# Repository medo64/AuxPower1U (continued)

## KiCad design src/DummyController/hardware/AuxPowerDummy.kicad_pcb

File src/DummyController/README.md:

# AuxPower1U: DummyController

Features:
* 5 DC inputs (input 1 has to be 9-15V)
* 5 DC outputs
* always connected output; no logic

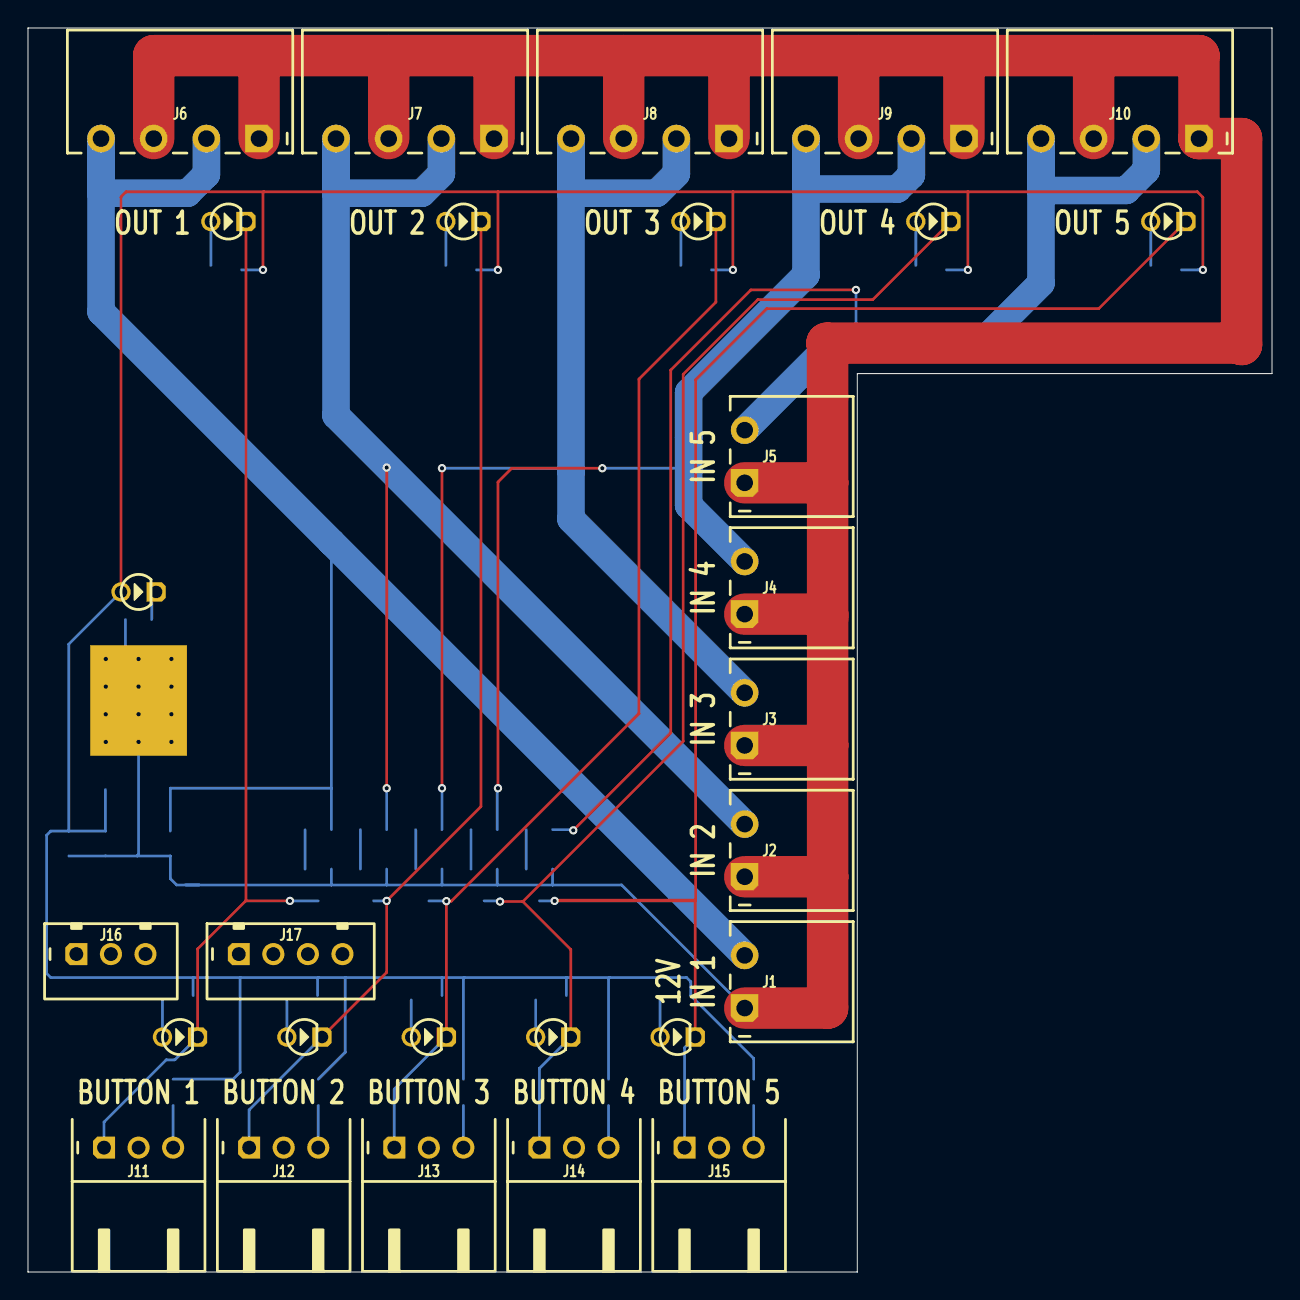
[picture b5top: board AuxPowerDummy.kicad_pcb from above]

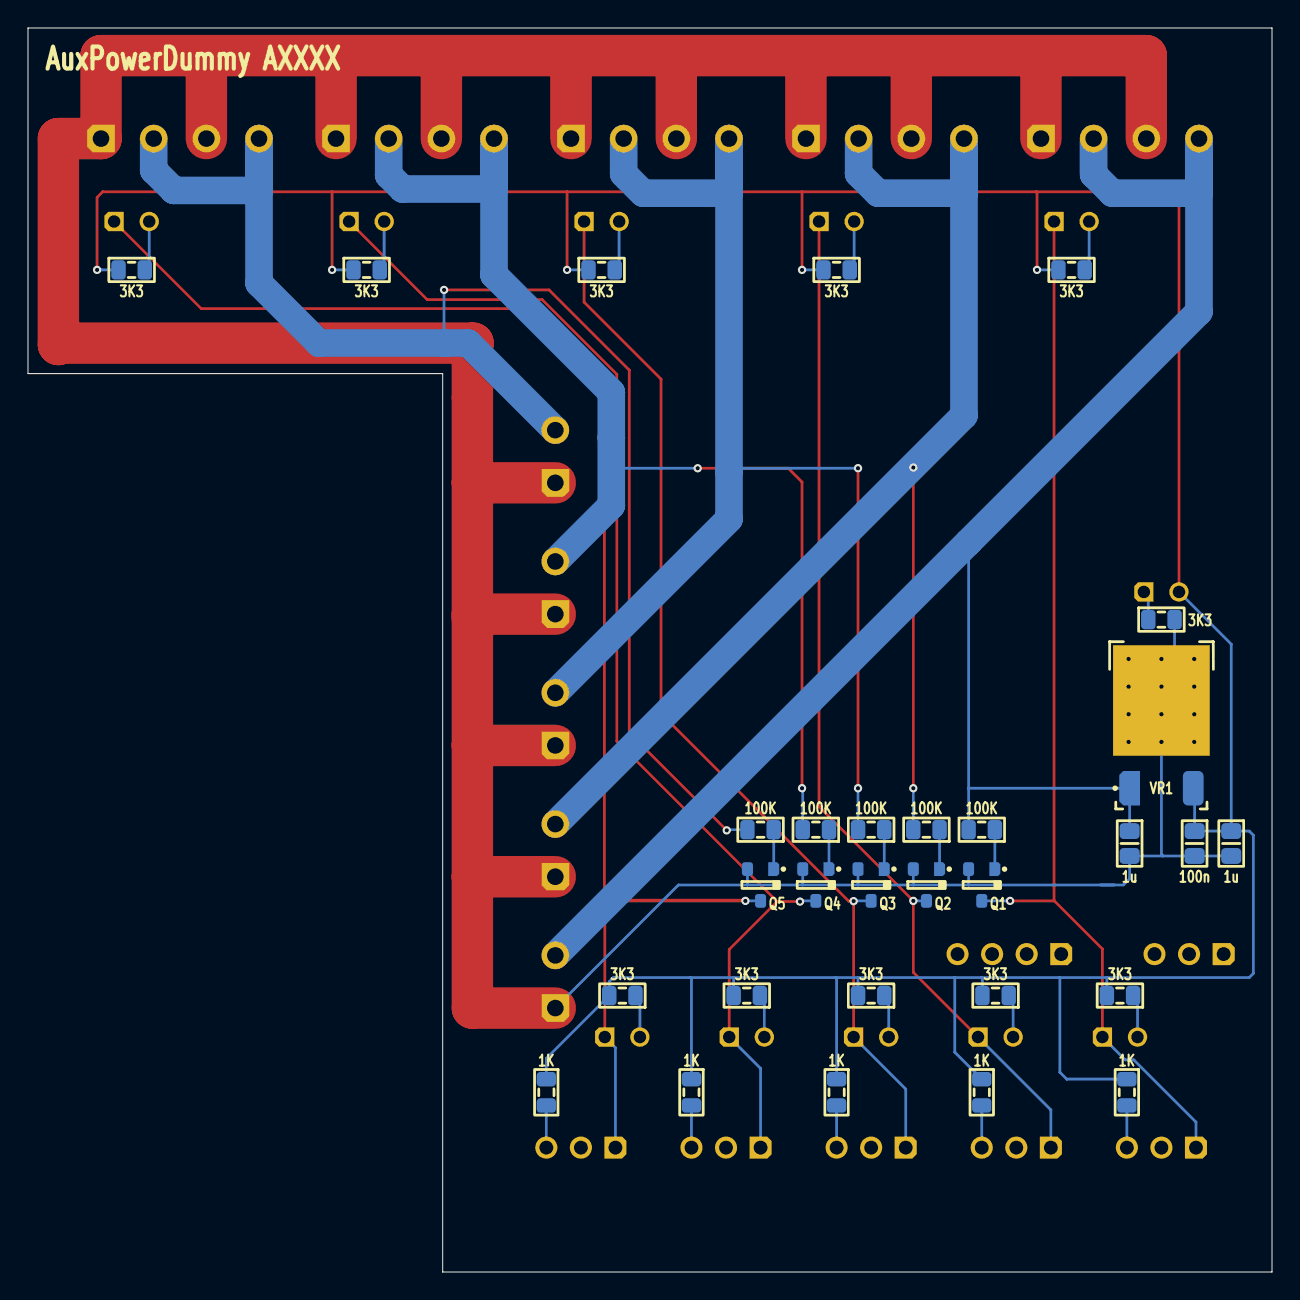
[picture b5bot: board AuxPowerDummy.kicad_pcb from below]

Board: 2 copper layers, 90.0 x 90.0 mm, 58 parts (30 on the bottom side), 33 nets.

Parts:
C1: 100n; C (0805)
C2, C3: 1u; C (0805)
DS1, DS2, DS3, DS4, DS5, DS6, DS7, DS8, DS9, DS10, DS11: LED; DS (D3.0)
J1, J2, J3, J4, J5: MC 1,5/2; J Phoenix MC (2w)
J6, J7, J8, J9, J10: MC 1,5/4; J Phoenix MC (4w)
J11, J12, J13, J14, J15: S3B-XH-A; J JST XH S (3w)
J16: B3B-XH-A; J JST XH B [UART] (3w)
J17: B4B-XH-A; J JST XH B [I2C] (4w)
Q1, Q2, Q3, Q4, Q5: BC846B,235; Q Transistor NPN (SOT23-3)
R1, R2, R3, R4, R5: 1K; R (0805)
R6, R7, R8, R9, R10, R11, R12, R13, R14, R15, R16: 3K3; R (0805)
R17, R18, R19, R20, R21: 100K; R (0805)
VR1: AS7805ADTR; VR Linear 5V 1000mA [AS7805ADTR-G1] (TO252-2')

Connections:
5V: C1.2, C3.2, DS11.2, R1.2, R2.2, R3.2, R4.2, R5.2, R6.2, R7.2, R8.2, R9.2, R10.2, R11.1, R12.1, R13.1, R14.1, R15.1, VR1.3
BASE_SW1: Q1.1, R17.2
BASE_SW2: Q2.1, R18.2
BASE_SW3: Q3.1, R19.2
BASE_SW4: Q4.1, R20.2
BASE_SW5: Q5.1, R21.2
BUTTON1_LED: J11.3, R1.1
BUTTON2_LED: J12.3, R2.1
BUTTON3_LED: J13.3, R3.1
BUTTON4_LED: J14.3, R4.1
BUTTON5_LED: J15.3, R5.1
GND: C1.1, C2.1, C3.1, J1.1, J2.1, J3.1, J4.1, J5.1, J6.1, J6.3, J7.1, J7.3, J8.1, J8.3, J9.1, J9.3, J10.1, J10.3, Q1.2, Q2.2, Q3.2, Q4.2, Q5.2, R16.1, VR1.2
GND_SW1: DS1.1, DS6.1, J11.1, Q1.3
GND_SW2: DS2.1, DS7.1, J12.1, Q2.3
GND_SW3: DS3.1, DS8.1, J13.1, Q3.3
GND_SW4: DS4.1, DS9.1, J14.1, Q4.3
GND_SW5: DS5.1, DS10.1, J15.1, Q5.3
INPUT1: C2.2, J1.2, J6.2, J6.4, R17.1, VR1.1
INPUT2: J2.2, J7.2, J7.4, R18.1
INPUT3: J3.2, J8.2, J8.4, R19.1
INPUT4: J4.2, J9.2, J9.4, R20.1
INPUT5: J5.2, J10.2, J10.4, R21.1
LED_BUTTON_INT_1: DS1.2, R11.2
LED_BUTTON_INT_2: DS2.2, R12.2
LED_BUTTON_INT_3: DS3.2, R13.2
LED_BUTTON_INT_4: DS4.2, R14.2
LED_BUTTON_INT_5: DS5.2, R15.2
LED_OUT1: DS6.2, R6.1
LED_OUT2: DS7.2, R7.1
LED_OUT3: DS8.2, R8.1
LED_OUT4: DS9.2, R9.1
LED_OUT5: DS10.2, R10.1
LED_POWER: DS11.1, R16.2

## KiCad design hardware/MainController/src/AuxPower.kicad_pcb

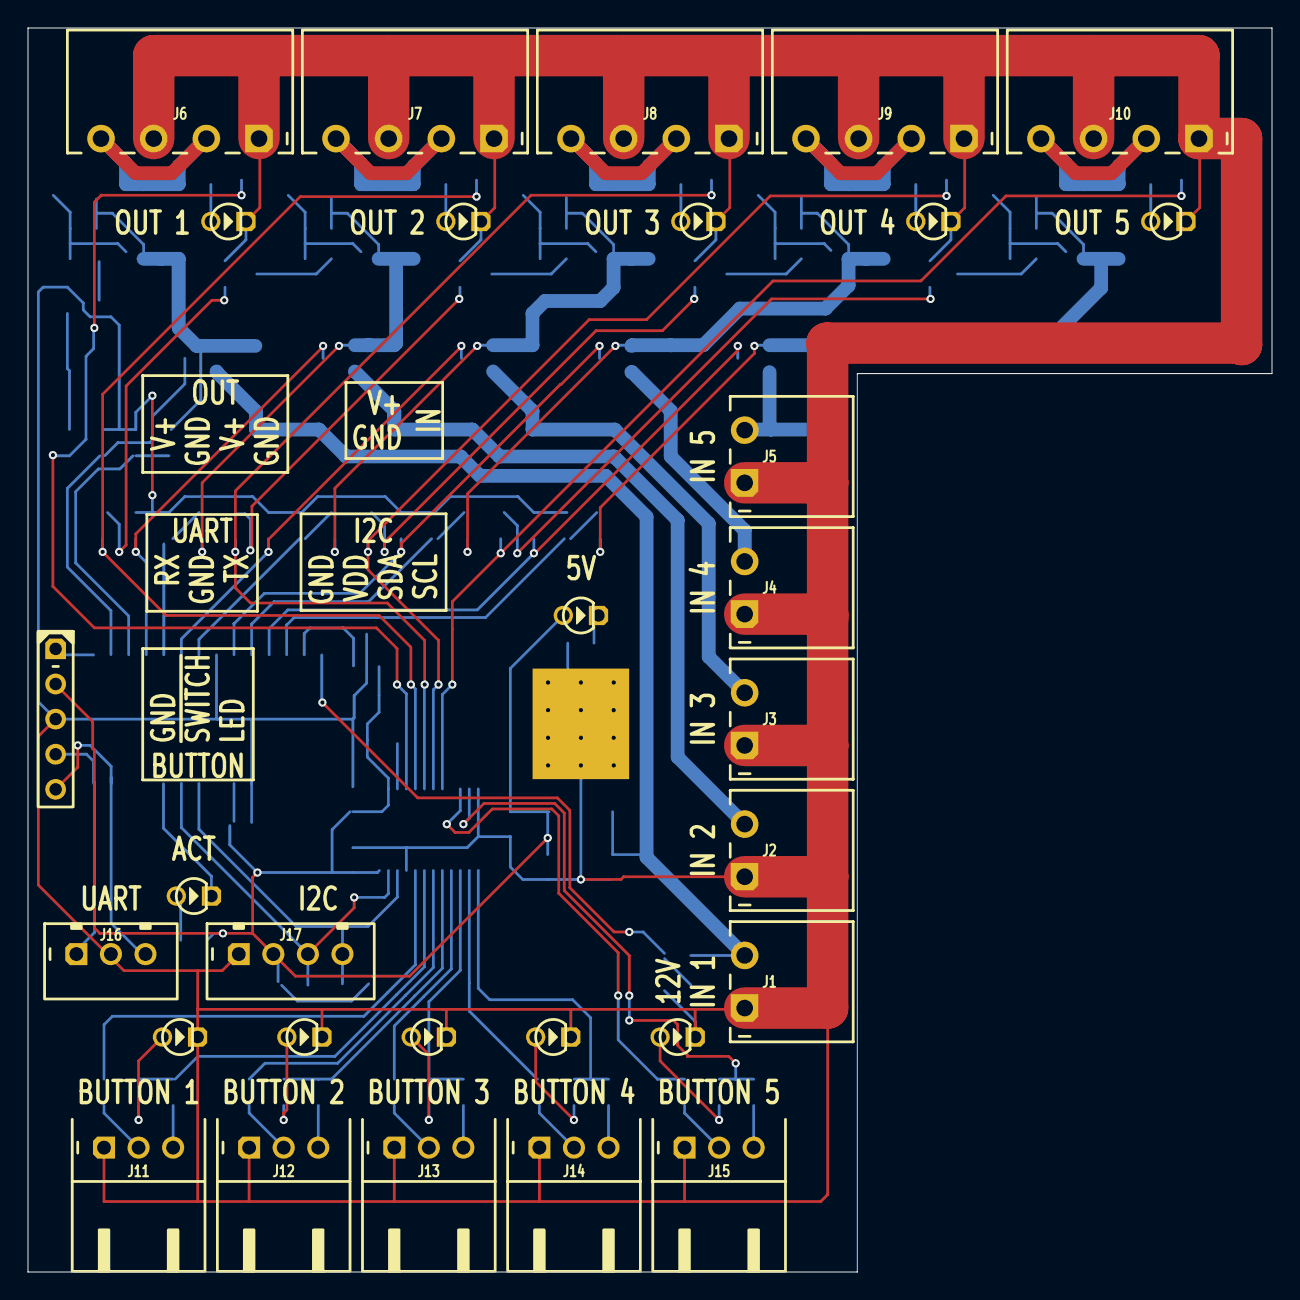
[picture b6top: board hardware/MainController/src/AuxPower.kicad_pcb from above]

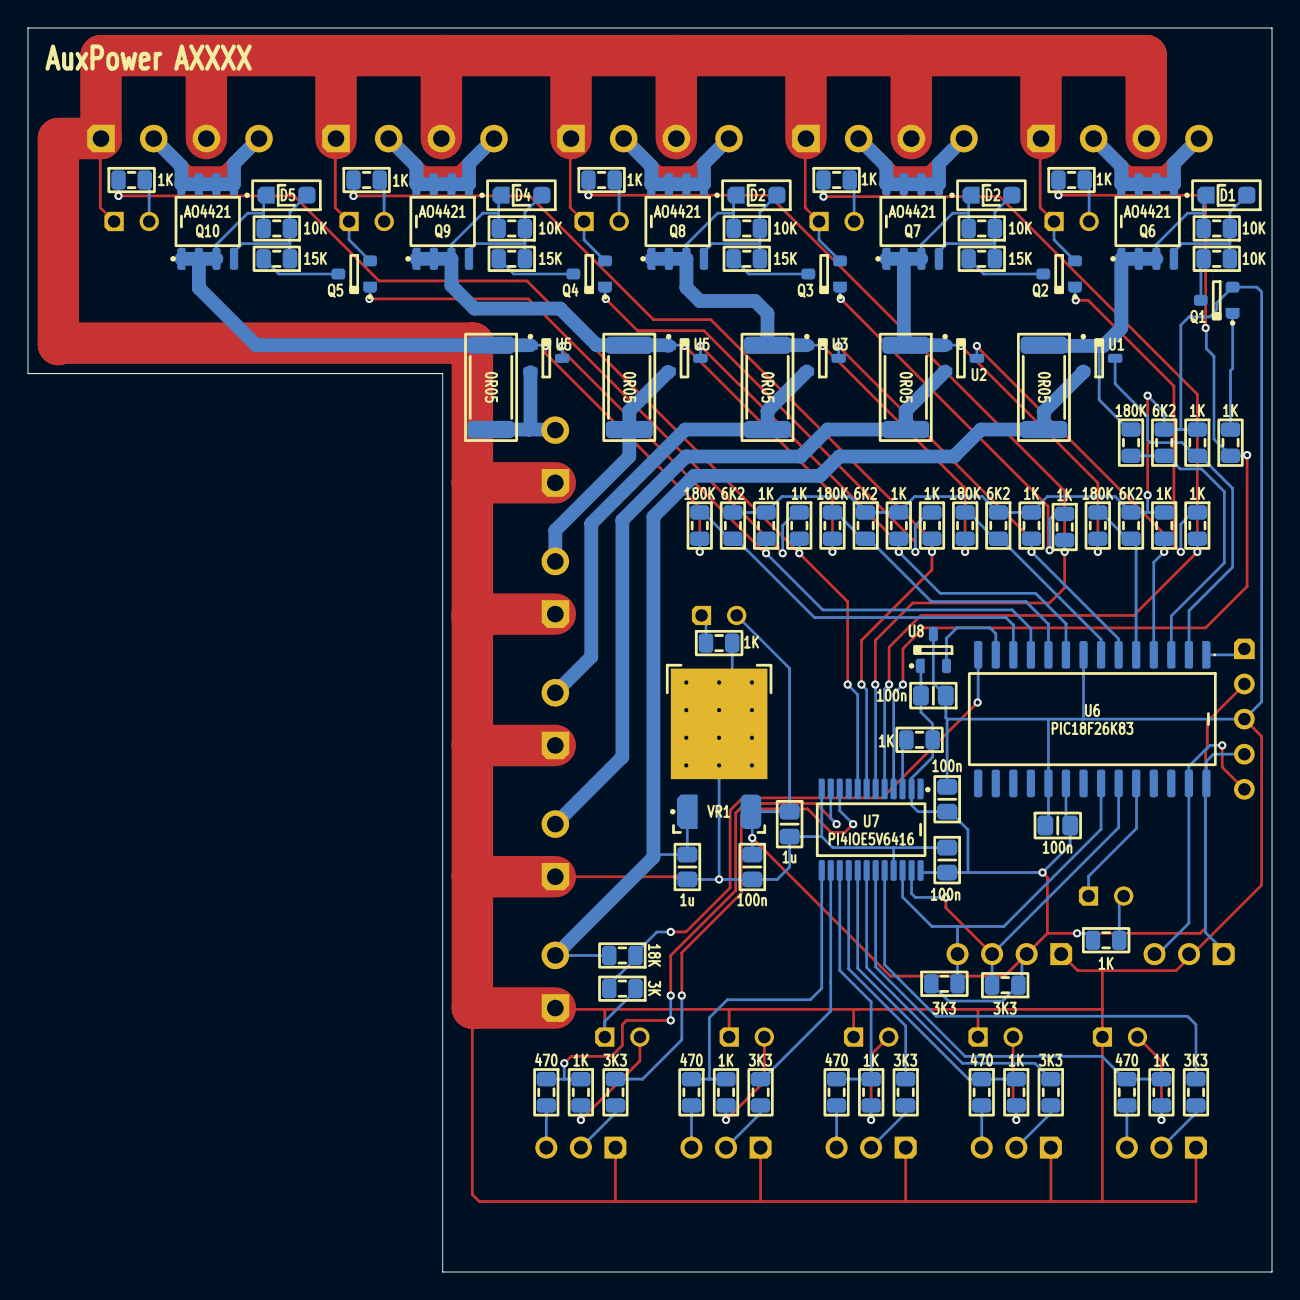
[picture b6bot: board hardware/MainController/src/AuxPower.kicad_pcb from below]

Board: 2 copper layers, 90.0 x 90.0 mm, 123 parts (93 on the bottom side), 88 nets.

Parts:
C1, C2, C3, C4, C5: 100n; C (0805)
C6, C7: 1u; C (0805)
D1, D2, D2#2, D4, D5: BZT52C12; D Zener (SOD123FL)
DS1, DS2, DS3, DS4, DS5, DS6, DS7, DS8, DS9, DS10, DS11, DS12: LED; DS (D3.0)
ICSP: Microchip PIC; ICSP PIC Pogo (5w)
J1, J2, J3, J4, J5: MC 1,5/2; J Phoenix MC (2w)
J6, J7, J8, J9, J10: MC 1,5/4; J Phoenix MC (4w)
J11, J12, J13, J14, J15: S3B-XH-A; J JST XH S (3w)
J16: B3B-XH-A; J JST XH B [UART] (3w)
J17: B4B-XH-A; J JST XH B [I2C] (4w)
Q1, Q2, Q3, Q4, Q5: BC846B,235; Q Transistor NPN (SOT23-3)
Q6, Q7, Q8, Q9, Q10: AO4421; Q MOSFET-P (SO-8)
R1, R2, R3, R4, R5: 0R05; R (2512)
R6, R7, R8, R9, R10: 470; R (0805)
R11, R12, R13, R14, R15, R16, R17, R18, R19, R20, R21, R22, R23, R24, R25, R26, R27, R28, R29, R30, R31, R32, R33: 1K; R (0805)
R34: 3K; R (0805)
R35, R36, R37, R38, R39, R40, R41: 3K3; R (0805)
R42, R43, R44, R45, R46: 6K2; R (0805)
R47, R48, R49, R50, R51, R52: 10K; R (0805)
R53, R54, R55, R56: 15K; R (0805)
R57: 18K; R (0805)
R58, R59, R60, R61, R62: 180K; R (0805)
U1, U2, U3, U5, U5#2: ZXCT1009; U Current Monitor [ZXCT1009] (SOT23-3)
U6: PIC18F26K83; U Micro [PIC18F26K83] (SOIC-28)
U7: PI4IOE5V6416; U Expander I2C [PI4IOE5V6416LEX] (TSSOP-24)
U8: MCP9701; U Temperature Analog [MCP9701] (SOT23-3)
VR1: AS7805ADTR; VR Linear 5V 1000mA [AS7805ADTR-G1] (TO252-2')

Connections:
5V: C1.2, C2.1, C3.1, C4.1, C5.1, C6.2, DS11.2, ICSP.2, J17.2, R32.2, R33.2, R40.2, R41.2, U6.20, U7.2, U7.24, U8.1, VR1.3
ADC_CURRENT1: R16.1, U1.3, U6.2
ADC_CURRENT2: R17.1, U2.3, U6.4
ADC_CURRENT3: R18.1, U3.3, U6.6
ADC_CURRENT4: R19.1, U5.3, U6.9
ADC_CURRENT5: R20.1, U5#2.3, U6.11
ADC_TEMPERATURE: U6.13, U8.2
ADC_VOLTAGE1: R42.1, R58.1, U6.3
ADC_VOLTAGE2: R43.1, R59.2, U6.5
ADC_VOLTAGE3: R44.1, R60.2, U6.7
ADC_VOLTAGE4: R45.1, R61.2, U6.10
ADC_VOLTAGE5: R46.1, R62.2, U6.12
ADC_VOLTAGE_IN: R34.1, R57.2, U6.14
BASE1: Q1.1, R11.1
BASE2: Q2.1, R12.2
BASE3: Q3.1, R13.2
BASE4: Q4.1, R14.2
BASE5: Q5.1, R15.2
BUTTON1_LED: J11.3, R6.1
BUTTON1_SWITCH: J11.2, R35.1
BUTTON2_LED: J12.3, R7.1
BUTTON2_SWITCH: J12.2, R36.1
BUTTON3_LED: J13.3, R8.1
BUTTON3_SWITCH: J13.2, R37.1
BUTTON4_LED: J14.3, R9.1
BUTTON4_SWITCH: J14.2, R38.1
BUTTON5_LED: J15.3, R10.1
BUTTON5_SWITCH: J15.2, R39.1
COLLECTOR1: Q1.3, R48.1
COLLECTOR2: Q2.3, R53.1
COLLECTOR3: Q3.3, R54.1
COLLECTOR4: Q4.3, R55.1
COLLECTOR5: Q5.3, R56.1
EXPANDER_RESET: R33.1, U7.3
GATE1: D1.2, Q6.4, R47.2, R48.2
GATE2: D2#2.2, Q7.4, R49.2, R53.2
GATE3: D2.2, Q8.4, R50.2, R54.2
GATE4: D4.2, Q9.4, R51.2, R55.2
GATE5: D5.2, Q10.4, R52.2, R56.2
GND: C1.1, C2.2, C3.2, C4.2, C5.2, C6.1, C7.1, DS1.1, DS2.1, DS3.1, DS4.1, DS5.1, DS6.1, DS7.1, DS8.1, DS9.1, DS10.1, ICSP.3, J1.1, J2.1, J3.1, J4.1, J5.1, J6.1, J6.3, J7.1, J7.3, J8.1, J8.3, J9.1, J9.3, J10.1, J10.3, J11.1, J12.1, J13.1, J14.1, J15.1, J16.2, J17.1, Q1.2, Q2.2, Q3.2, Q4.2, Q5.2, R16.2, R17.2, R18.2, R19.2, R20.2, R31.1, R34.2, R42.2, R43.2, R44.2, R45.2, R46.2, U6.8, U6.19, U7.12, U7.21, U8.3, VR1.2
I2C_SCL: J17.4, R41.1, U6.22, U7.22
I2C_SDA: J17.3, R40.1, U6.23, U7.23
ICSP_VPP: ICSP.1, U6.1
INPUT1: C7.2, J1.2, R1.1, R57.1, U1.2, VR1.1
INPUT1': D1.1, Q6.1, Q6.2, Q6.3, R1.2, R47.1, R58.2, U1.1
INPUT2: J2.2, R2.1, U2.2
INPUT2': D2#2.1, Q7.1, Q7.2, Q7.3, R2.2, R49.1, R59.1, U2.1
INPUT3: J3.2, R3.1, U3.2
INPUT3': D2.1, Q8.1, Q8.2, Q8.3, R3.2, R50.1, R60.1, U3.1
INPUT4: J4.2, R4.1, U5.2
INPUT4': D4.1, Q9.1, Q9.2, Q9.3, R4.2, R51.1, R61.1, U5.1
INPUT5: J5.2, R5.1, U5#2.2
INPUT5': D5.1, Q10.1, Q10.2, Q10.3, R5.2, R52.1, R62.1, U5#2.1
IN_BUTTON1_SWITCH: R35.2, U7.20
IN_BUTTON2_SWITCH: R36.2, U7.18
IN_BUTTON3_SWITCH: R37.2, U7.16
IN_BUTTON4_SWITCH: R38.2, U7.14
IN_BUTTON5_SWITCH: R39.2, U7.10
LED_ACTIVITY: DS12.2, R32.1
LED_BUTTON_INT_1: DS1.2, R26.1
LED_BUTTON_INT_2: DS2.2, R27.1
LED_BUTTON_INT_3: DS3.2, R28.1
LED_BUTTON_INT_4: DS4.2, R29.1
LED_BUTTON_INT_5: DS5.2, R30.1
LED_OUT_1: DS6.2, R21.1
LED_OUT_2: DS7.2, R22.1
LED_OUT_3: DS8.2, R23.1
LED_OUT_4: DS9.2, R24.1
LED_OUT_5: DS10.2, R25.1
LED_POWER: DS11.1, R31.2
OUTPUT1: J6.2, J6.4, Q6.5, Q6.6, Q6.7, Q6.8
OUTPUT2: J7.2, J7.4, Q7.5, Q7.6, Q7.7, Q7.8
OUTPUT3: J8.2, J8.4, Q8.5, Q8.6, Q8.7, Q8.8
OUTPUT4: J9.2, J9.4, Q9.5, Q9.6, Q9.7, Q9.8
OUTPUT5: J10.2, J10.4, Q10.5, Q10.6, Q10.7, Q10.8
OUT_ACTIVITY: DS12.1, U6.24
OUT_BUTTON1_LED: R6.2, R26.2, U7.19
OUT_BUTTON2_LED: R7.2, R27.2, U7.17
OUT_BUTTON3_LED: R8.2, R28.2, U7.15
OUT_BUTTON4_LED: R9.2, R29.2, U7.13
OUT_BUTTON5_LED: R10.2, R30.2, U7.11
OUT_OUTPUT1: R11.2, R21.2, U7.4
OUT_OUTPUT2: R12.1, R22.2, U7.5
OUT_OUTPUT3: R13.1, R23.2, U7.6
OUT_OUTPUT4: R14.1, R24.2, U7.7
OUT_OUTPUT5: R15.1, R25.2, U7.8
UART_RX ICSP_DAT: ICSP.4, J16.1, U6.28
UART_TX ICSP_CLK: ICSP.5, J16.3, U6.27

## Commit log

2024-08-17 Added DellTrigger sub-project
2024-08-17 Added aluminium plate model
2024-08-17 Added fan controller
2024-08-17 Fancontroller supports 4 fans
2024-08-18 Added requirements
2024-08-18 Added features
2024-08-18 Added DellTrigger schematics
2024-08-18 Added case selection
2024-08-18 Minor changes
2024-08-18 Added FanController schematics
2024-08-19 Changed DellTrigger diode to zener
2024-08-20 Added AC grommet
2024-08-20 Fixed hole diameter to 2.5mm
2024-08-21 Replaced MCP9700A with MCP9701A
2024-08-22 Added initial AuxPower
2024-08-23 Adjusted resistors a bit
2024-08-23 Added part list for controller
2024-08-23 Swapped PIC for SOIC variant
2024-08-23 Fixed fan connector count on FanController
2024-08-27 Moved silkscreen descriptions a bit
2024-08-27 Moving directory
2024-08-27 Updated models to have PTH holes on both sides
2024-08-27 Updated PTH components to have soldermask opening on both sides
2024-08-27 Moved GND line to look nicer
2024-08-29 Increasing resistors to account for 55V supply
2024-08-29 Added equipment setup
2024-08-29 Redesigned FanController board
2024-08-29 Renaming blog posts
2024-08-29 Added more explanation for DellTrigger
2024-08-29 Added UPS description
2024-08-30 Added AC grommet model
2024-08-30 Added OLED model
2024-09-01 Updated oled chasis tolerances
2024-09-01 Added alignment blocks
2024-09-02 Updated OLED model
2024-09-07 Additional OLED model update
2024-09-08 Added DellTrigger test
2024-09-09 Added shroud to alignment blocks
2024-09-11 Added case retainers
2024-09-11 Renamed drill template file
2024-09-12 Resizing PS retainers a bit
2024-09-12 Added chamfer to PS clips top
2024-09-12 A bit more messing with PS retainers
2024-09-13 More model updates
2024-09-14 Updated PS rails to be full length
2024-09-14 Added fan braces
2024-09-14 Add fan back brace (needs rework)
2024-09-14 Updated DC drill template
2024-09-14 Added alu plate fixup
2024-09-15 Refactoring fan brace
2024-09-15 Adjusted drill template for DC
2024-09-15 Added PCB case models
2024-09-15 Changed drill size for aluminium plate
2024-09-15 Adding parts
2024-09-15 Refactoring PCB retainer model
2024-09-15 Added extra parts
2024-09-16 Added stopped to OLED model
2024-09-16 Added fixup for audio 3.5mm jack
2024-09-17 Adjusted depth for main controller box
2024-09-17 Added PS story to docs
2024-09-17 Deeper cutouts for edge connectors
2024-09-17 Cutting edges some more
2024-09-17 More adjusting for PCB boxes
2024-09-18 Reorganizing directories
2024-09-18 Initial FanController project
2024-09-19 Adjusted PWM behavior
2024-09-19 FanController: temperature sensitive code
2024-09-19 Using moving average
2024-09-19 Updated 12F1501 model
2024-09-19 Added pin usage table for FanController
2024-09-19 Added pin usage for MainController
2024-09-22 Adjusted rail model to have pass-through for fan wires
2024-09-22 MainController: Fixing components
2024-09-22 MainController: Moved Activity LED a bit
2024-09-22 MainController: initial blink
2024-09-22 MainController: added ticker
2024-09-23 Initial working OLED communication
2024-09-23 Shortening code a bit
2024-09-23 Adding cooling blog post
2024-09-23 Refactoring file names
2024-09-23 Added IO expander outputs
2024-09-23 Added button input
2024-09-23 Refactoring i2c functions
2024-09-24 MainController: parametrising 18F module
2024-09-24 Readded I2c master code for PIC16F1454
2024-09-24 MainController: Added summary page
2024-09-25 MainController: Added ADC measurements
2024-09-26 Updated PIC
2024-09-26 Added test mode
2024-09-26 MainController: Adding forgotten 1K to GND for current monitor
2024-09-26 MainController: adjusting trace widths a bit
2024-09-26 MainController: enter test mode by holding button 1 and 5 together
2024-09-26 MainController: added usage
2024-09-27 Added wire colors
2024-09-27 Adding inverse writing for OLED
2024-09-27 Added progress bar
2024-09-27 Rounding all values up
2024-09-27 Added 8x averaging
2024-09-27 Bigger progress bar
2024-09-28 Added first fan controller post
2024-09-28 MainController: added open-drain outputs for rev B
2024-09-29 MainController: making output open-drain
2024-09-29 MainController: Changed transistor base resistor to 10K
2024-09-29 MainController: double-sampling ADC
2024-09-29 MainController: test mode shows display rate
2024-09-29 Added 5V reading to tests
2024-09-29 MainController: added die temperature reading to test mode
2024-09-29 MainController: Changed ZXCT1009 to HV7801
2024-09-29 Slighlty higher wattage resistor to cover for 8A range
2024-09-29 MainController: moved UART lines
2024-09-29 FanController: updated startup sequence
2024-09-29 MainController: Updated silkscreen
2024-09-30 Initial code for button handling
2024-09-30 Front LED state follows buttons
2024-09-30 MainController: added markers for channels that are on
2024-09-30 MainController: double-click to close summary
2024-10-02 Setting output together with LEDs
2024-10-02 Fixed OLED blinking
2024-10-02 MainController: fixing LEDs after reset from off state
2024-10-02 MainController: no need for setting LED and out manually
2024-10-03 MainController: prepping for settings load/save
2024-10-03 MainController: adjusting voltage dividers
2024-10-06 FanController: Both 1x4 and 2x2 variants available
2024-10-07 FanController: added post
2024-10-09 MainController: added settings save/load
2024-10-12 fixed typo
2024-10-12 Added basic UART and start of PPS
2024-10-12 Improved PPS
2024-10-12 Finished UART output
2024-10-12 MainController: added UART input
2024-10-13 MainController: added I UART command
2024-10-13 MainController: adjusting communication a bit
2024-10-13 MainController: fixed display bug
2024-10-13 MainController: Refactoring Uart
2024-10-13 MainController: added blinking
2024-10-13 MainController: channels that are off have different background
2024-10-15 MainController: increased speed to 200 kHz
2024-10-15 MainController: Updated I2C master settings
2024-10-16 MainController: updated SSD1306
2024-10-17 Added audio connector pinout
2024-10-17 MainController: Replaced main mosfet
2024-10-17 MainController: fixed part number
2024-10-17 MainController: added vent holes to PCB holder
2024-10-20 MainController: Refactoring PCB holder bottom pockets
2024-10-20 MainController: extra side venting holes
2024-10-20 MainController: rounded bottom pockets
2024-10-20 MainController: refactoring PCB holder vents
2024-10-20 MainController: Adjusted resistor values for MOSFET drive
2024-10-20 MainController: Reducing internal LED brightness
2024-10-20 MainController: Reducing brightness for output LEDs
2024-10-20 MainController: speeding up state transits (was 5s, now 3s)
2024-10-20 MainController: added software protection for open-drain outputs
2024-10-29 MainController: A bit wider side PCB holder
2024-11-03 MainController: updated refdes
2024-11-03 Prepped for rev B
2024-11-03 MainController: Moving voltage for PIC after shunt resistor
2024-11-03 MainController: moved silkscreen
2024-11-03 MainController: adjusted multipliers
2024-11-03 MainController: added software current limiter
2024-11-03 MainController: agressive filtering when reading close to 0
2024-11-04 Adjusted ADC voltage to 1.024 and changed voltage ratio to 64:1
2024-11-04 Updated components to match new ratios
2024-11-04 MainController: adjusted current ratio
2024-11-04 MainController: removed extra variables
2024-11-11 DummyController: first version
2024-11-13 MainController: Added missing trace
2024-11-13 MainController: adding power limit per channel
2024-11-13 MainController: minor changes
2024-11-13 Updated equipment with LED colors
2024-11-13 MainController: increased power limit slightly to prevent false triggers
2024-11-13 MainController: power can be toggled instead of just turned off
2024-11-14 Moved 12V input before sense line
2024-11-14 Removed blog posts
2024-11-14 Increased trace width for power
2024-11-14 MainController: added extra hole to PCB holder model
2024-11-15 MainController: moved ICSP in case model
2024-11-15 MainController: smaller side vent
2024-11-15 MainController: added brace
2024-11-15 MainController: added brace hole
2024-11-16 MainController: reduces ICSP hole height for PCB case
2024-11-16 MainController: If output is off, go directly into power on mode
2024-11-16 MainController: faster startup time
2024-11-16 MainController: minor corrections to PCB case
2024-11-16 Updated equipment list resistor values
2024-11-16 MainController: wider GND traces
2025-01-11 Adjusted ADC resistors
2025-01-12 Adjusted resistor for button color
2025-01-12 Fixed connector dimensions for NetGear GS305EPP
2025-07-14 Fixed links
2025-07-15 Refactoring to use PhotoMOS (not completed)
2025-07-15 Reconnected all broken traces
2025-07-16 Cleaning up a bit
2025-07-16 Updated aluminium plate specification
2025-07-16 Trace cleanup
2025-07-16 Removed dummy controller
2025-07-19 Moved fan controller to AuxFanController repo
2025-07-19 Migrated DellPowerTrigger to a separate repository
2025-07-19 Reorganizing files a bit
2025-07-24 Initial case setup 3D model
2025-07-24 Added button backplate
2025-07-25 Refactored the whole board to have switches in airflow direction
2025-07-25 Updating models
2025-07-25 Moved Bud PRM-14460 to a separate directory
2025-07-25 Updated PF19AL1UD1 case models
2025-07-26 Adjusted drill templates a bit
2025-07-26 Strenghtening the front rail
2025-07-26 Adjusting drilling template
2025-07-26 Fixed back rail alignment
2025-07-26 Added initial fan model
2025-07-27 Added mounting hole
2025-07-27 Added PCB controller model
2025-07-27 Adjusted controller PCB enclosure
2025-08-04 Thinner grommets (6mm)
2025-08-17 Lowered rails a bit
2025-08-18 Adjusted AC grommet
2025-08-26 Updated assembly instructions
2025-08-30 Reverse fan mount
2025-08-30 Moved case components to src/case
2025-08-30 Updated footprints
2025-08-30 Fixed output LEDS
2025-08-30 Made compatible with CPC1706Y
2025-08-31 Cleanup a bit
2025-08-31 Updated controller case
2025-08-31 Reverse fan mount (blowing in)
2025-08-31 Added crimp terminals
2025-08-31 Swapped OLED pinout to match 128x64 order
2025-08-31 Added I2C resistor marking
2025-09-01 Adjusted grommed
2025-09-01 Updated equipment
2025-09-01 Updated output control pins
2025-09-01 Added delay for OLED initialization (needed for some displays)
2025-09-01 Added display off after inactivity
2025-09-01 Fixed temperature overflow
2025-09-01 Added different limits per channel
2025-09-15 Fixed PhotoMOS refdes
2025-09-21 Fixed current monitor part name
2025-09-21 Adjusted current monitor resistor for 1:1 ratio
2025-09-21 Updated photomos refdes
2025-09-21 Removed HV7801 resistor
2025-09-21 Reduced power limits a bit
2025-09-21 Refactoring measurement setup
2025-09-21 Adjusted reset to show measurement during reset
2025-09-23 Cleaning up safety limits
